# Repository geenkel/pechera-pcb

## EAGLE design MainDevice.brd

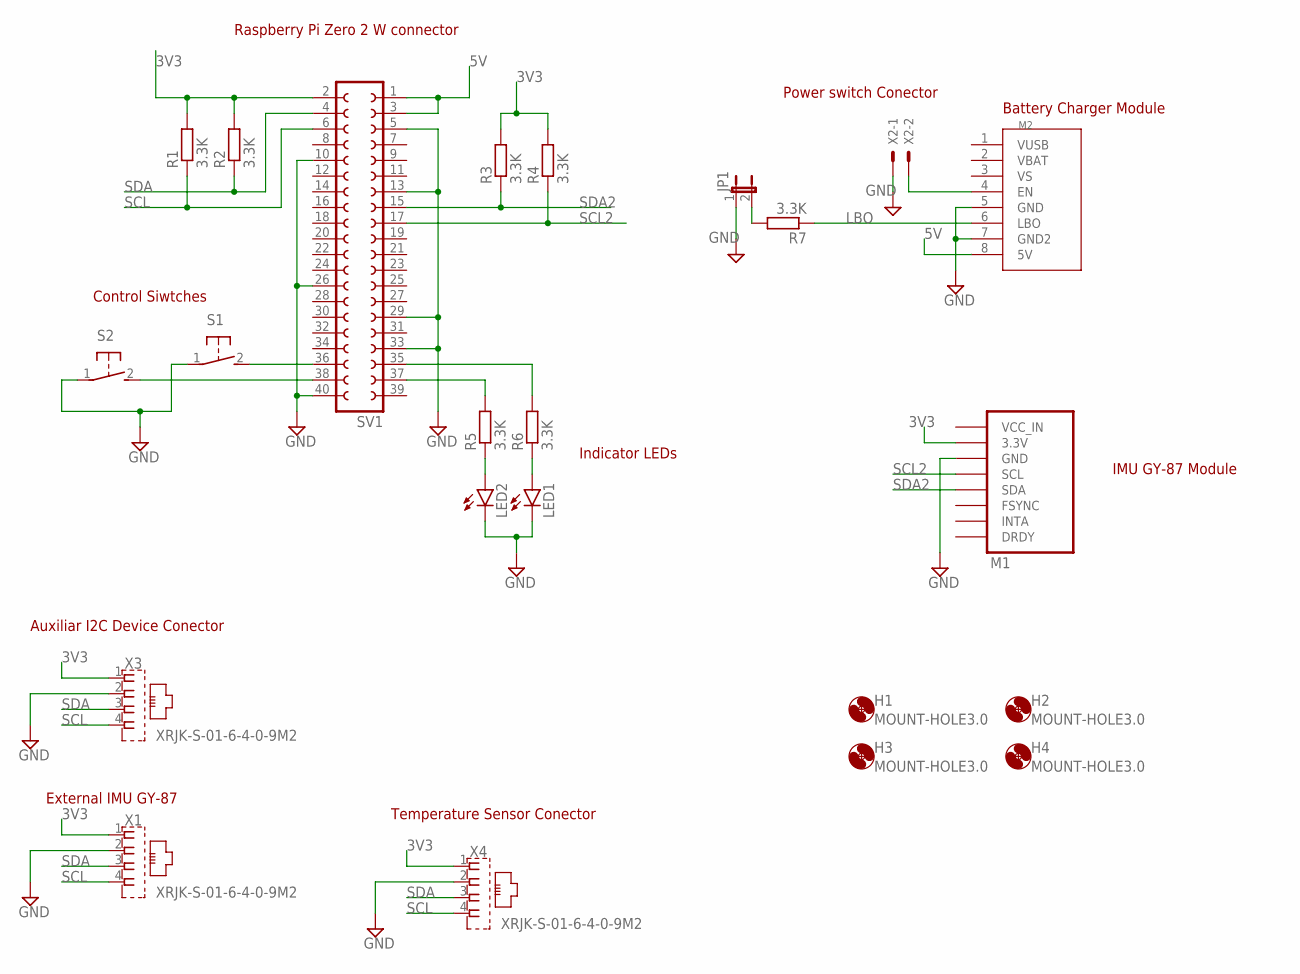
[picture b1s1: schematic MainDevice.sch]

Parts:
H1, H2, H3, H4: MOUNT-HOLE3.0; 3,0
JP1: JP1E; JP1
LED1, LED2: LED5MM
M1: GY-87
M2: POWERBOOST_1000C
R1, R2, R3, R4, R5, R6, R7: 3.3K; R0805
S1, S2: 31-XX; B3F-31XX
SV1: FE20-2
X1, X3, X4: XRJK-S-01-6-4-0-9M2
X2: 22-23-2021

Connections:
3V3: M1.2 (3.3V), R1.2, R2.2, R3.2, R4.2, SV1.2, X1.1, X3.1, X4.1
5V: M2.8 (5V), SV1.1, SV1.3
GND: JP1.1, LED1.K (C), LED2.K (C), M1.3 (GND), M2.5 (GND), M2.7 (GND2), S1.1, S2.1, SV1.5, SV1.10, SV1.13, SV1.26, SV1.29, SV1.33, SV1.40, X1.2, X2.1, X3.2, X4.2
LBO: M2.6 (LBO), R7.1
unnamed: S1.2 (S), SV1.36
unnamed: S2.2 (S), SV1.38
unnamed: M2.4 (EN), X2.2
unnamed: LED2.A, R5.1
unnamed: LED1.A, R6.1
unnamed: JP1.2, R7.2
unnamed: R6.2, SV1.35
unnamed: R5.2, SV1.37
SCL: R1.1, SV1.6, X1.4, X3.4, X4.4
SCL2: M1.4 (SCL), R4.1, SV1.17
SDA: R2.1, SV1.4, X1.3, X3.3, X4.3
SDA2: M1.5 (SDA), R3.1, SV1.15

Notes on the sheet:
Battery Charger Module
Power switch Conector
IMU GY-87 Module
External IMU GY-87
Temperature Sensor Conector
Auxiliar I2C Device Conector
Raspberry Pi Zero 2 W connector
Control Siwtches
Indicator LEDs

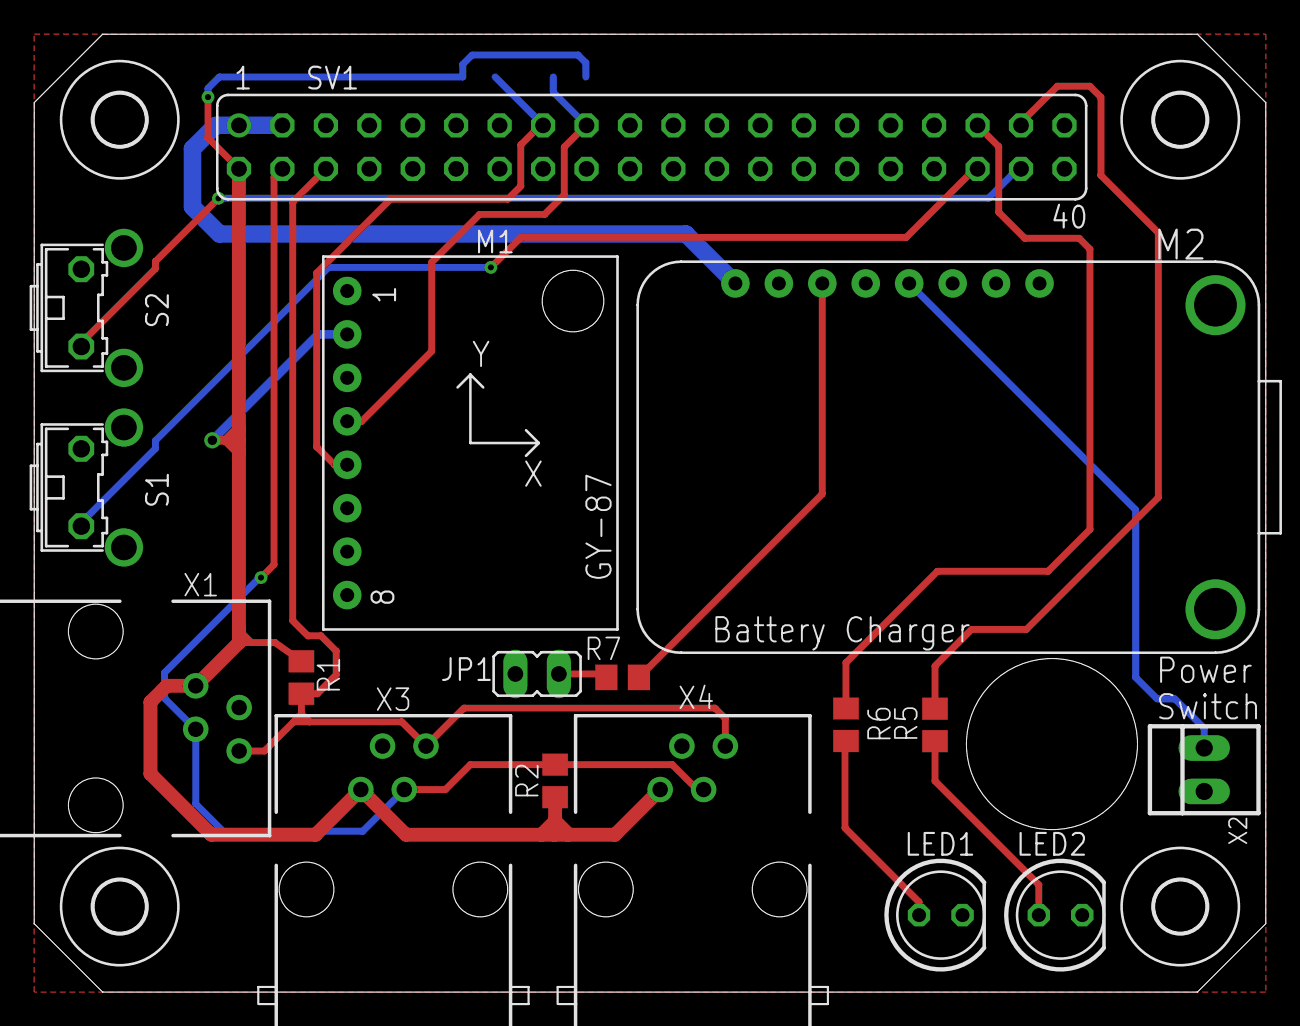
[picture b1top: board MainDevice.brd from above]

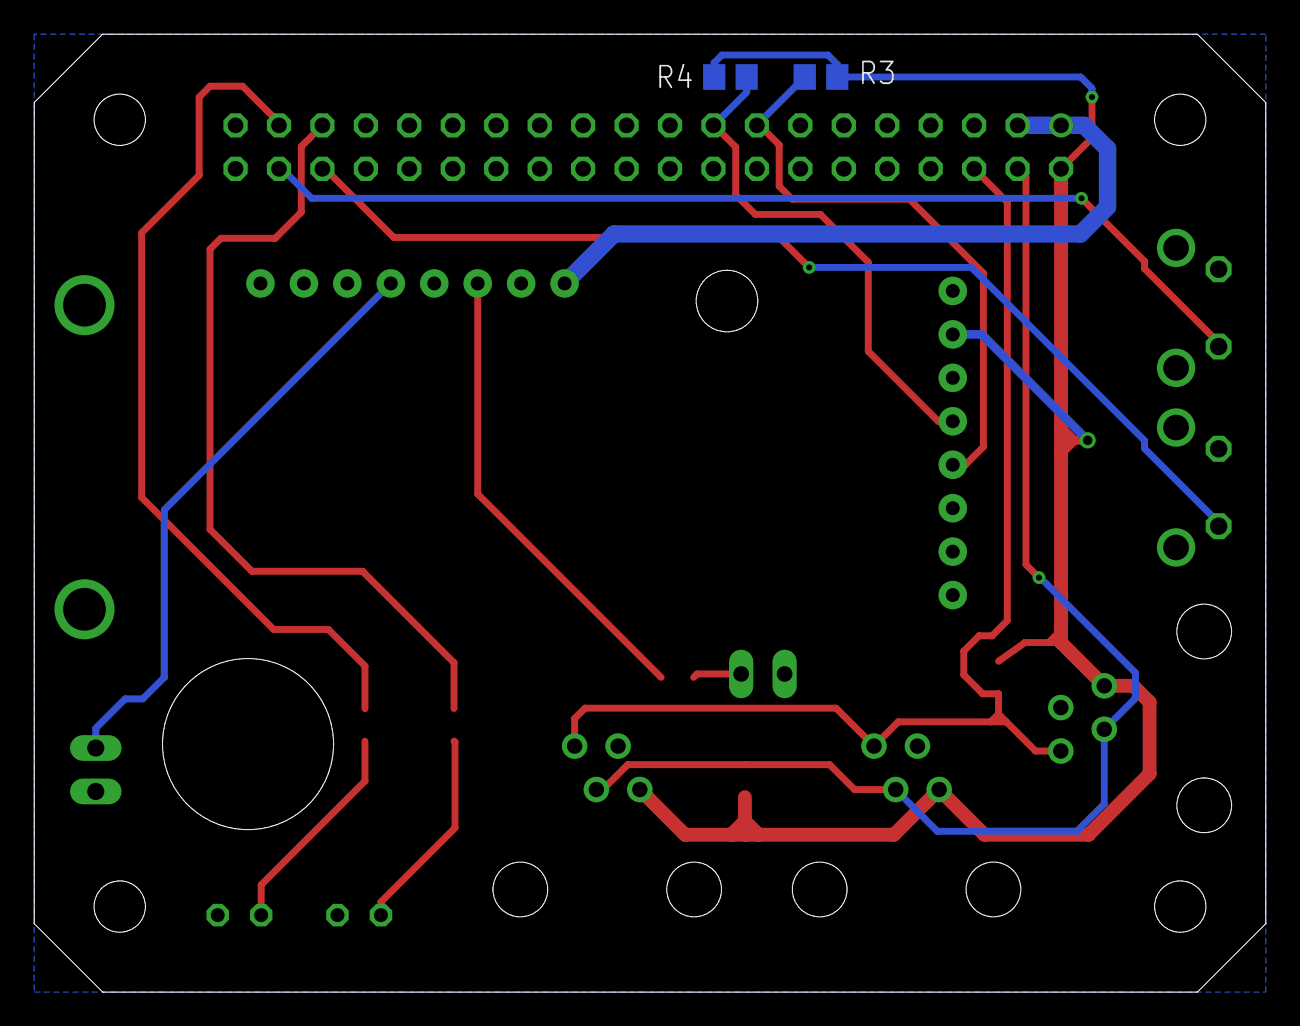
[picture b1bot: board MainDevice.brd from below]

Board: 2 copper layers, 72.0 x 56.0 mm, 23 parts (2 on the bottom side), 16 nets.

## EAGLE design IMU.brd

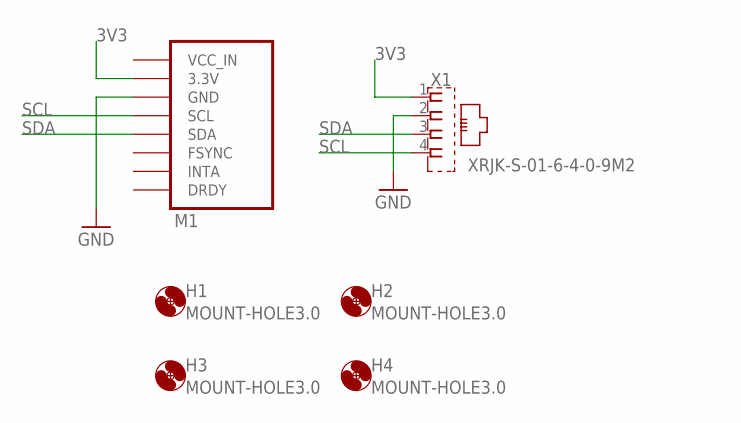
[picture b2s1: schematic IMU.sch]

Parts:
H1, H2, H3, H4: MOUNT-HOLE3.0; 3,0
M1: GY-87
X1: XRJK-S-01-6-4-0-9M2

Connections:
3V3: M1.2 (3.3V), X1.1
GND: M1.3 (GND), X1.2
SCL: M1.4 (SCL), X1.4
SDA: M1.5 (SDA), X1.3

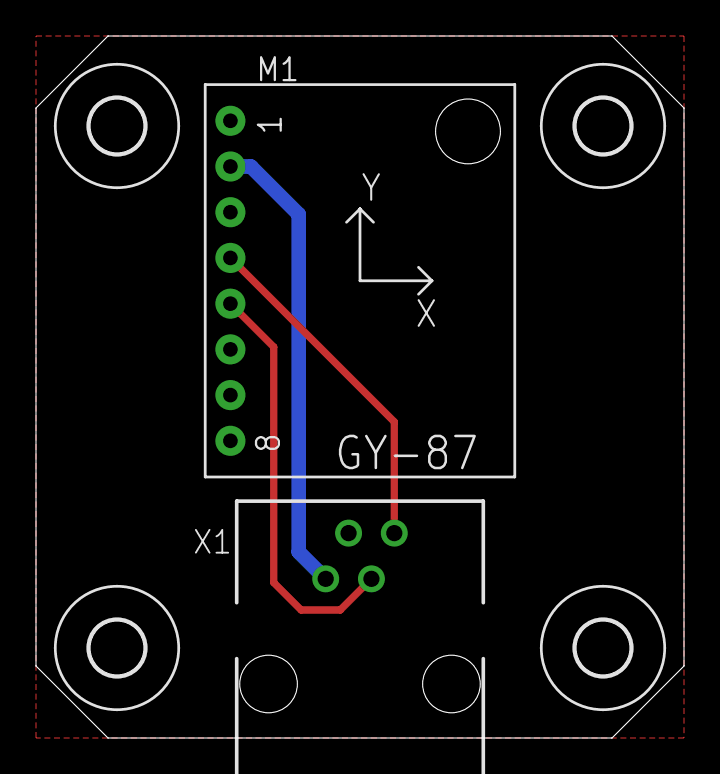
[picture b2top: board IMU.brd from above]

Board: 2 copper layers, 36.0 x 39.0 mm, 6 parts (0 on the bottom side), 4 nets.

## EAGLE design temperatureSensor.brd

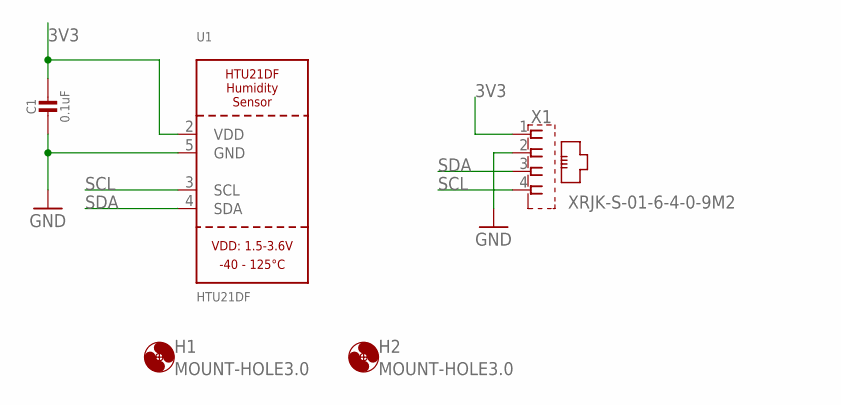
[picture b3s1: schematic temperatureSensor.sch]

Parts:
C1: 0.1uF; 0805-NO
H1, H2: MOUNT-HOLE3.0; 3,0
U1: HTU21DF
X1: XRJK-S-01-6-4-0-9M2

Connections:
3V3: C1.1, U1.2 (VDD), X1.1
GND: C1.2, U1.5 (GND), X1.2
SCL: U1.3 (SCL), X1.4
SDA: U1.4 (SDA), X1.3

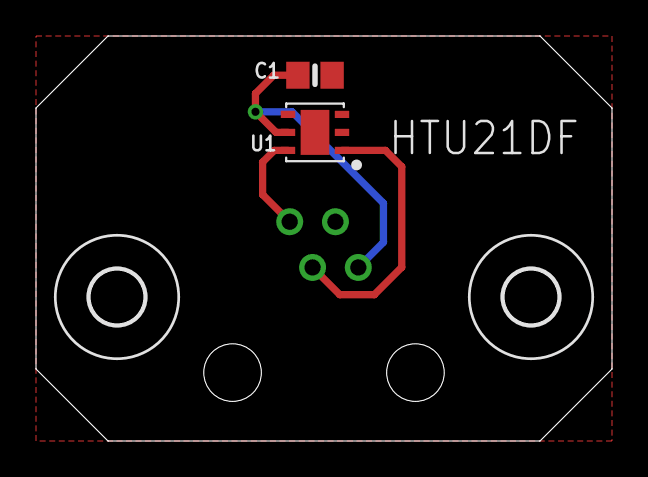
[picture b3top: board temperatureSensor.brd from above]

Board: 2 copper layers, 32.0 x 22.5 mm, 5 parts (1 on the bottom side), 4 nets.

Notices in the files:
parts and their libraries:
microbuilder: This work is placed in the public domain, and may be freely used for commercial and non-commercial work with the following conditions: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
